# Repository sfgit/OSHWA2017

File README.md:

# OSHWA2017
Badges for open source hardware association summit 2017

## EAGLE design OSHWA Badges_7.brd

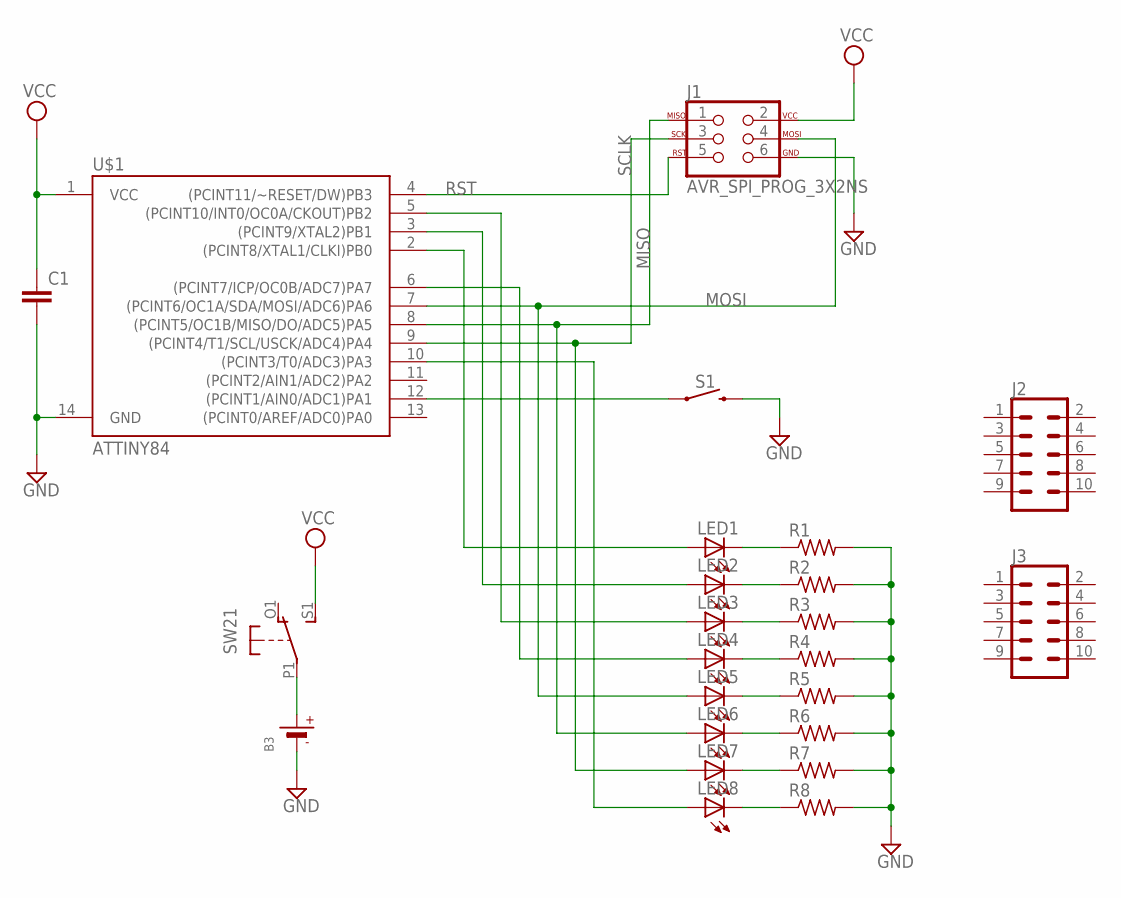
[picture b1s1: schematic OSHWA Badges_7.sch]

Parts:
B3: BATTERYCR2032_BAT-HLD-001; CR2032_SMT_BAT-HLD-001
C1: C-EUC0805K; C0805K
J1: AVR_SPI_PROG_3X2NS; 2X3-NS
J2, J3: CONN_05X2NO_SILK; 2X5_NOSILK
LED1, LED2, LED3, LED4, LED5, LED6, LED7, LED8: LEDCHIPLED_0805; CHIPLED_0805
R1, R2, R3, R4, R5, R6, R7, R8: R-US_M0805; M0805
S1: MOMENTARY-SWITCH-SPST-PTH-6.0MM-KIT; TACTILE_SWITCH_PTH_6.0MM_KIT
SW2: DPDT-EG1390; EG1390
U$1: ATTINY84; SO14

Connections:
GND: B3.-, C1.2, J1.6, R1.2, R2.2, R3.2, R4.2, R5.2, R6.2, R7.2, R8.2, S1.3 (2), U$1.14 (GND)
MISO: J1.1, LED6.A, U$1.8 ((PCINT5/OC1B/MISO/DO/ADC5)PA5)
MOSI: J1.4, LED5.A, U$1.7 ((PCINT6/OC1A/SDA/MOSI/ADC6)PA6)
unnamed: LED1.C, R1.1
unnamed: LED2.C, R2.1
unnamed: LED3.C, R3.1
unnamed: LED4.C, R4.1
unnamed: LED5.C, R5.1
unnamed: LED6.C, R6.1
unnamed: LED7.C, R7.1
unnamed: LED8.C, R8.1
unnamed: LED1.A, U$1.2 ((PCINT8/XTAL1/CLKI)PB0)
unnamed: LED2.A, U$1.3 ((PCINT9/XTAL2)PB1)
unnamed: LED3.A, U$1.5 ((PCINT10/INT0/OC0A/CKOUT)PB2)
unnamed: LED4.A, U$1.6 ((PCINT7/ICP/OC0B/ADC7)PA7)
unnamed: LED8.A, U$1.10 ((PCINT3/T0/ADC3)PA3)
unnamed: B3.+$1 (+), B3.+$2 (+), SW2.P1
unnamed: S1.1, U$1.12 ((PCINT1/AIN0/ADC1)PA1)
RST: J1.5, U$1.4 ((PCINT11/~RESET/DW)PB3)
SCLK: J1.3, LED7.A, U$1.9 ((PCINT4/T1/SCL/USCK/ADC4)PA4)
VCC: C1.1, J1.2, SW2.S1 (S), U$1.1 (VCC)

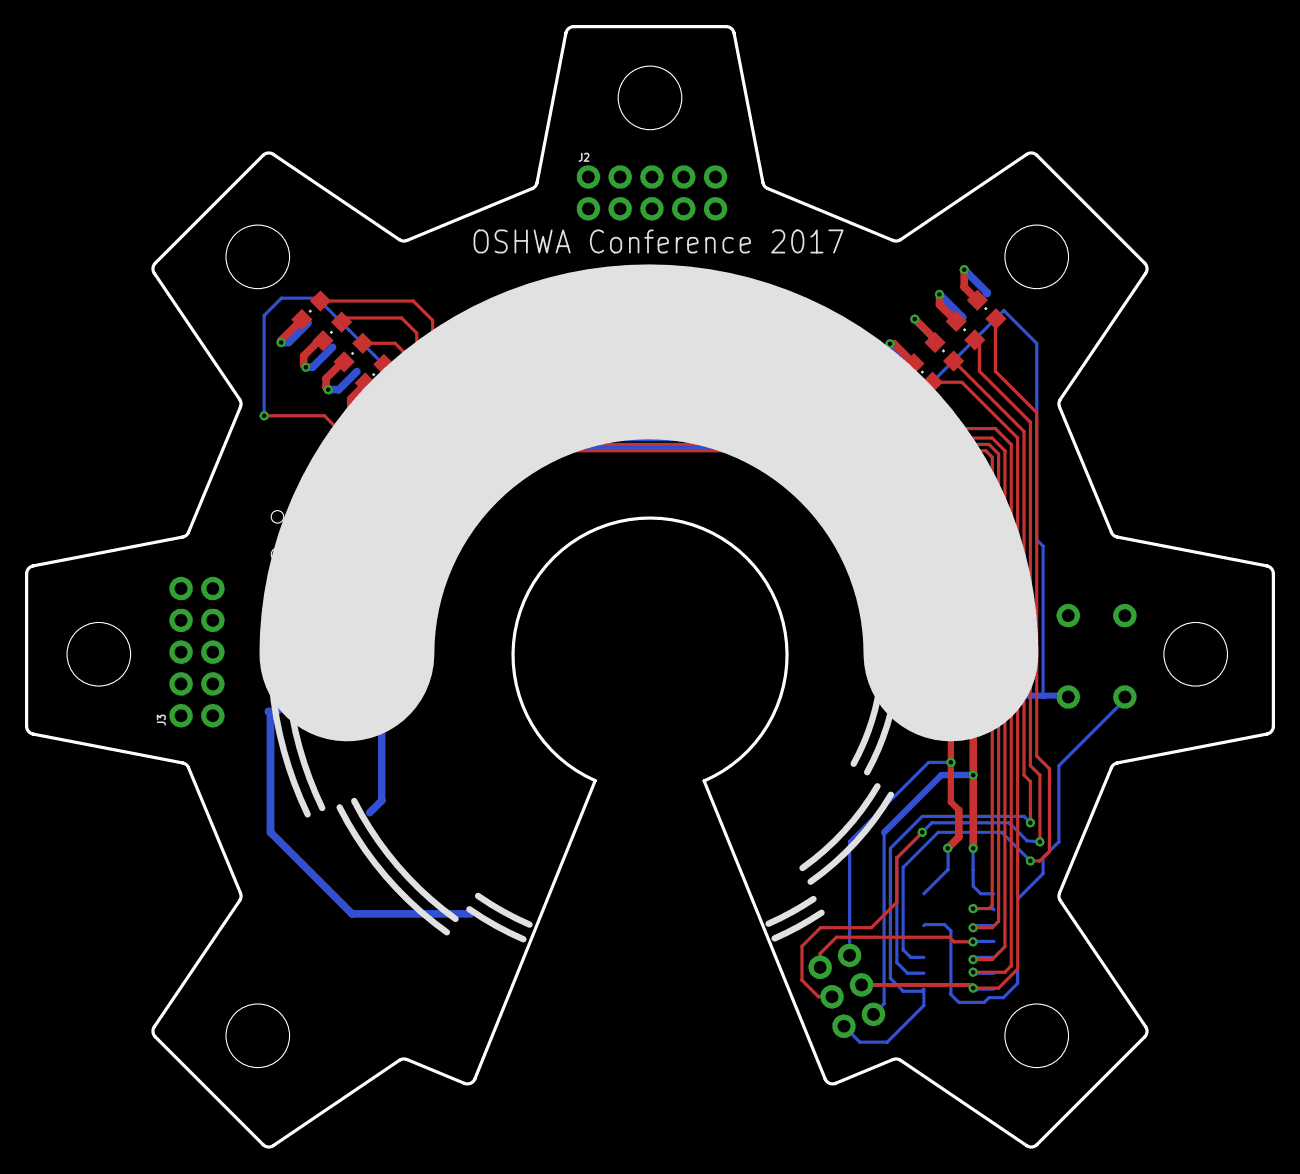
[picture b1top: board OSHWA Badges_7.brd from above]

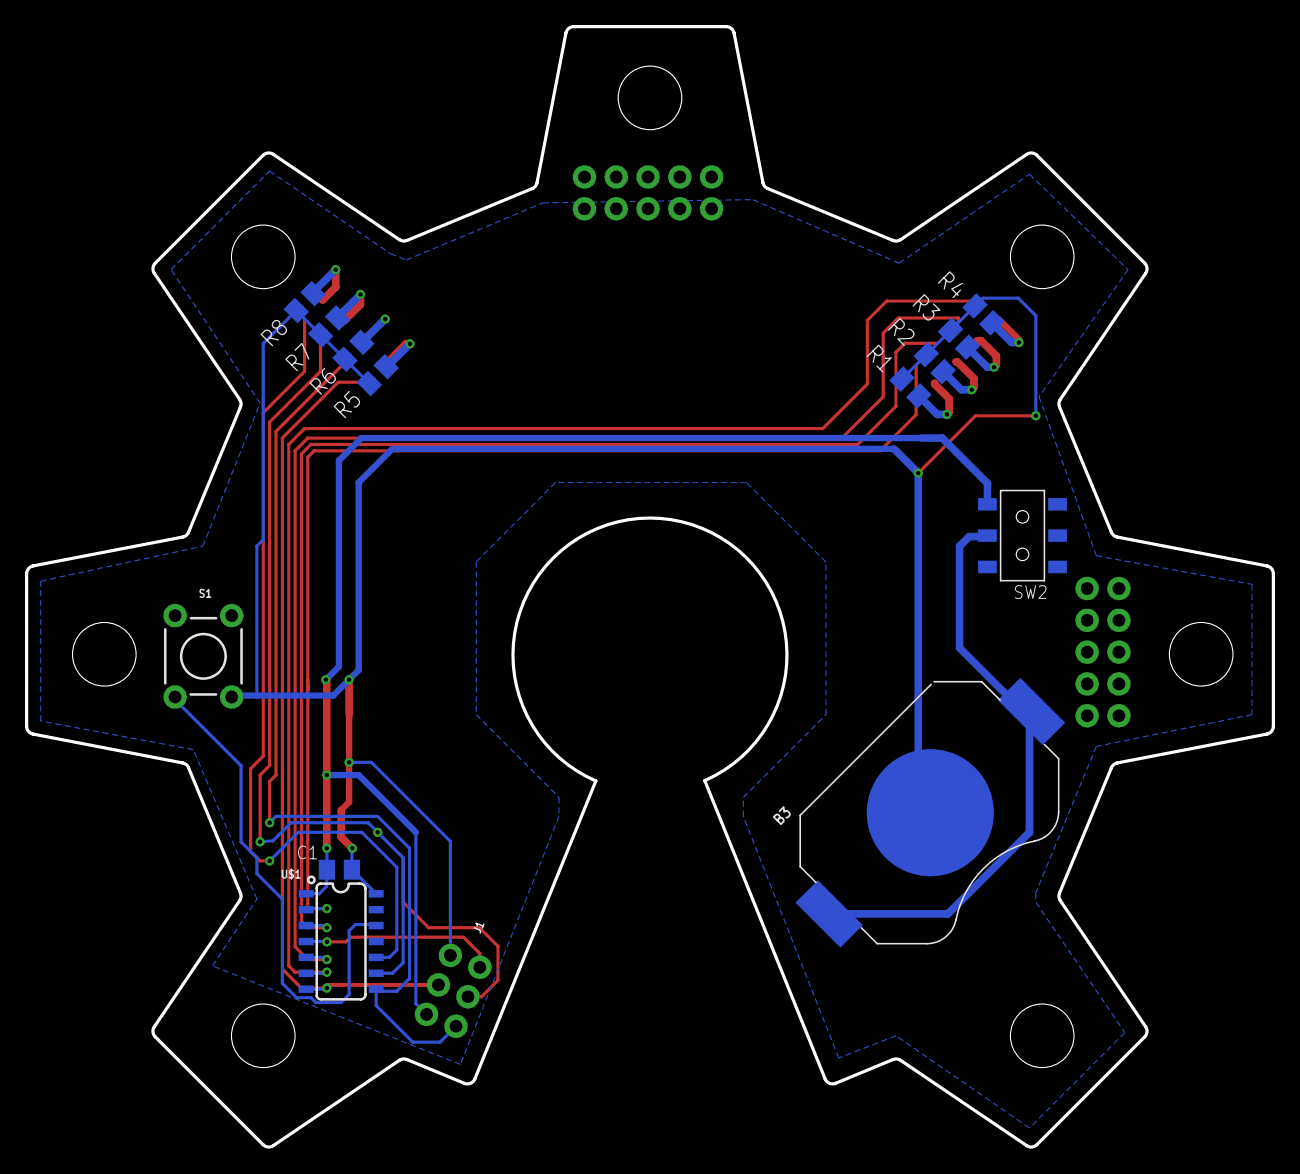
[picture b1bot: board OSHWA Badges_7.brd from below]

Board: 2 copper layers, 99.6 x 89.5 mm, 24 parts (14 on the bottom side), 21 nets.

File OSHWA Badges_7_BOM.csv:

"Part";"Value";"Device";"Package";"Description";"PROD_ID";"SF_SKU";"VALUE";
"B3";"";"BATTERYCR2032_BAT-HLD-001";"CR2032_SMT_BAT-HLD-001";"CR1220 SMT - Digikey: 3001K-ND";"";"";"";
"C1";"";"C-EUC0805K";"C0805K";"CAPACITOR, European symbol";"";"";"";
"J1";"AVR_SPI_PROG_3X2NS";"AVR_SPI_PROG_3X2NS";"2X3-NS";"AVR ISP 6 Pin";"";"";"";
"J2";"";"CONN_05X2NO_SILK";"2X5_NOSILK";"Multi connection point. Often used as Generic Header-pin footprint for 0.1 inch spaced/style header connections";"";"";"";
"J3";"";"CONN_05X2NO_SILK";"2X5_NOSILK";"Multi connection point. Often used as Generic Header-pin footprint for 0.1 inch spaced/style header connections";"";"";"";
"LED1";"";"LEDCHIPLED_0805";"CHIPLED_0805";"LED";"";"";"";
"LED2";"";"LEDCHIPLED_0805";"CHIPLED_0805";"LED";"";"";"";
"LED3";"";"LEDCHIPLED_0805";"CHIPLED_0805";"LED";"";"";"";
"LED4";"";"LEDCHIPLED_0805";"CHIPLED_0805";"LED";"";"";"";
"LED5";"";"LEDCHIPLED_0805";"CHIPLED_0805";"LED";"";"";"";
"LED6";"";"LEDCHIPLED_0805";"CHIPLED_0805";"LED";"";"";"";
"LED7";"";"LEDCHIPLED_0805";"CHIPLED_0805";"LED";"";"";"";
"LED8";"";"LEDCHIPLED_0805";"CHIPLED_0805";"LED";"";"";"";
"R1";"";"R-US_M0805";"M0805";"RESISTOR, American symbol";"";"";"";
"R2";"";"R-US_M0805";"M0805";"RESISTOR, American symbol";"";"";"";
"R3";"";"R-US_M0805";"M0805";"RESISTOR, American symbol";"";"";"";
"R4";"";"R-US_M0805";"M0805";"RESISTOR, American symbol";"";"";"";
"R5";"";"R-US_M0805";"M0805";"RESISTOR, American symbol";"";"";"";
"R6";"";"R-US_M0805";"M0805";"RESISTOR, American symbol";"";"";"";
"R7";"";"R-US_M0805";"M0805";"RESISTOR, American symbol";"";"";"";
"R8";"";"R-US_M0805";"M0805";"RESISTOR, American symbol";"";"";"";
"S1";"MOMENTARY-SWITCH-SPST-PTH-6.0MM-KIT";"MOMENTARY-SWITCH-SPST-PTH-6.0MM-KIT";"TACTILE_SWITCH_PTH_6.0MM_KIT";"Momentary Switch (Pushbutton) - SPST";"SWCH-08441";"COM-00097 ";"";
"SW2";"";"DPDT-EG1390";"EG1390";"";"";"";"";
"U$1";"ATTINY84";"ATTINY84";"SO14";"Atmel 14-pin 2/4/8kB flash uC";"IC-11285";"";"ATTINY84";

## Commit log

2017-10-05 Uploading EAGLE Schematic and PCB Files (EAGLE v7 Format)
2017-10-05 Test firmware for the ATTINY84 (using Arduino Uno as the programmer)
2017-10-06 Uploading stencil set from OSHWA conference.
2017-12-02 Adding board shape and BOM files

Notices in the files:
parts and their libraries:
SparkFun-IC-Microcontroller: Licensing: Creative Commons ShareAlike 4.0 International - https://creativecommons.org/licenses/by-sa/4.0
microbuilder: This work is placed in the public domain, and may be freely used for commercial and non-commercial work with the following conditions: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
